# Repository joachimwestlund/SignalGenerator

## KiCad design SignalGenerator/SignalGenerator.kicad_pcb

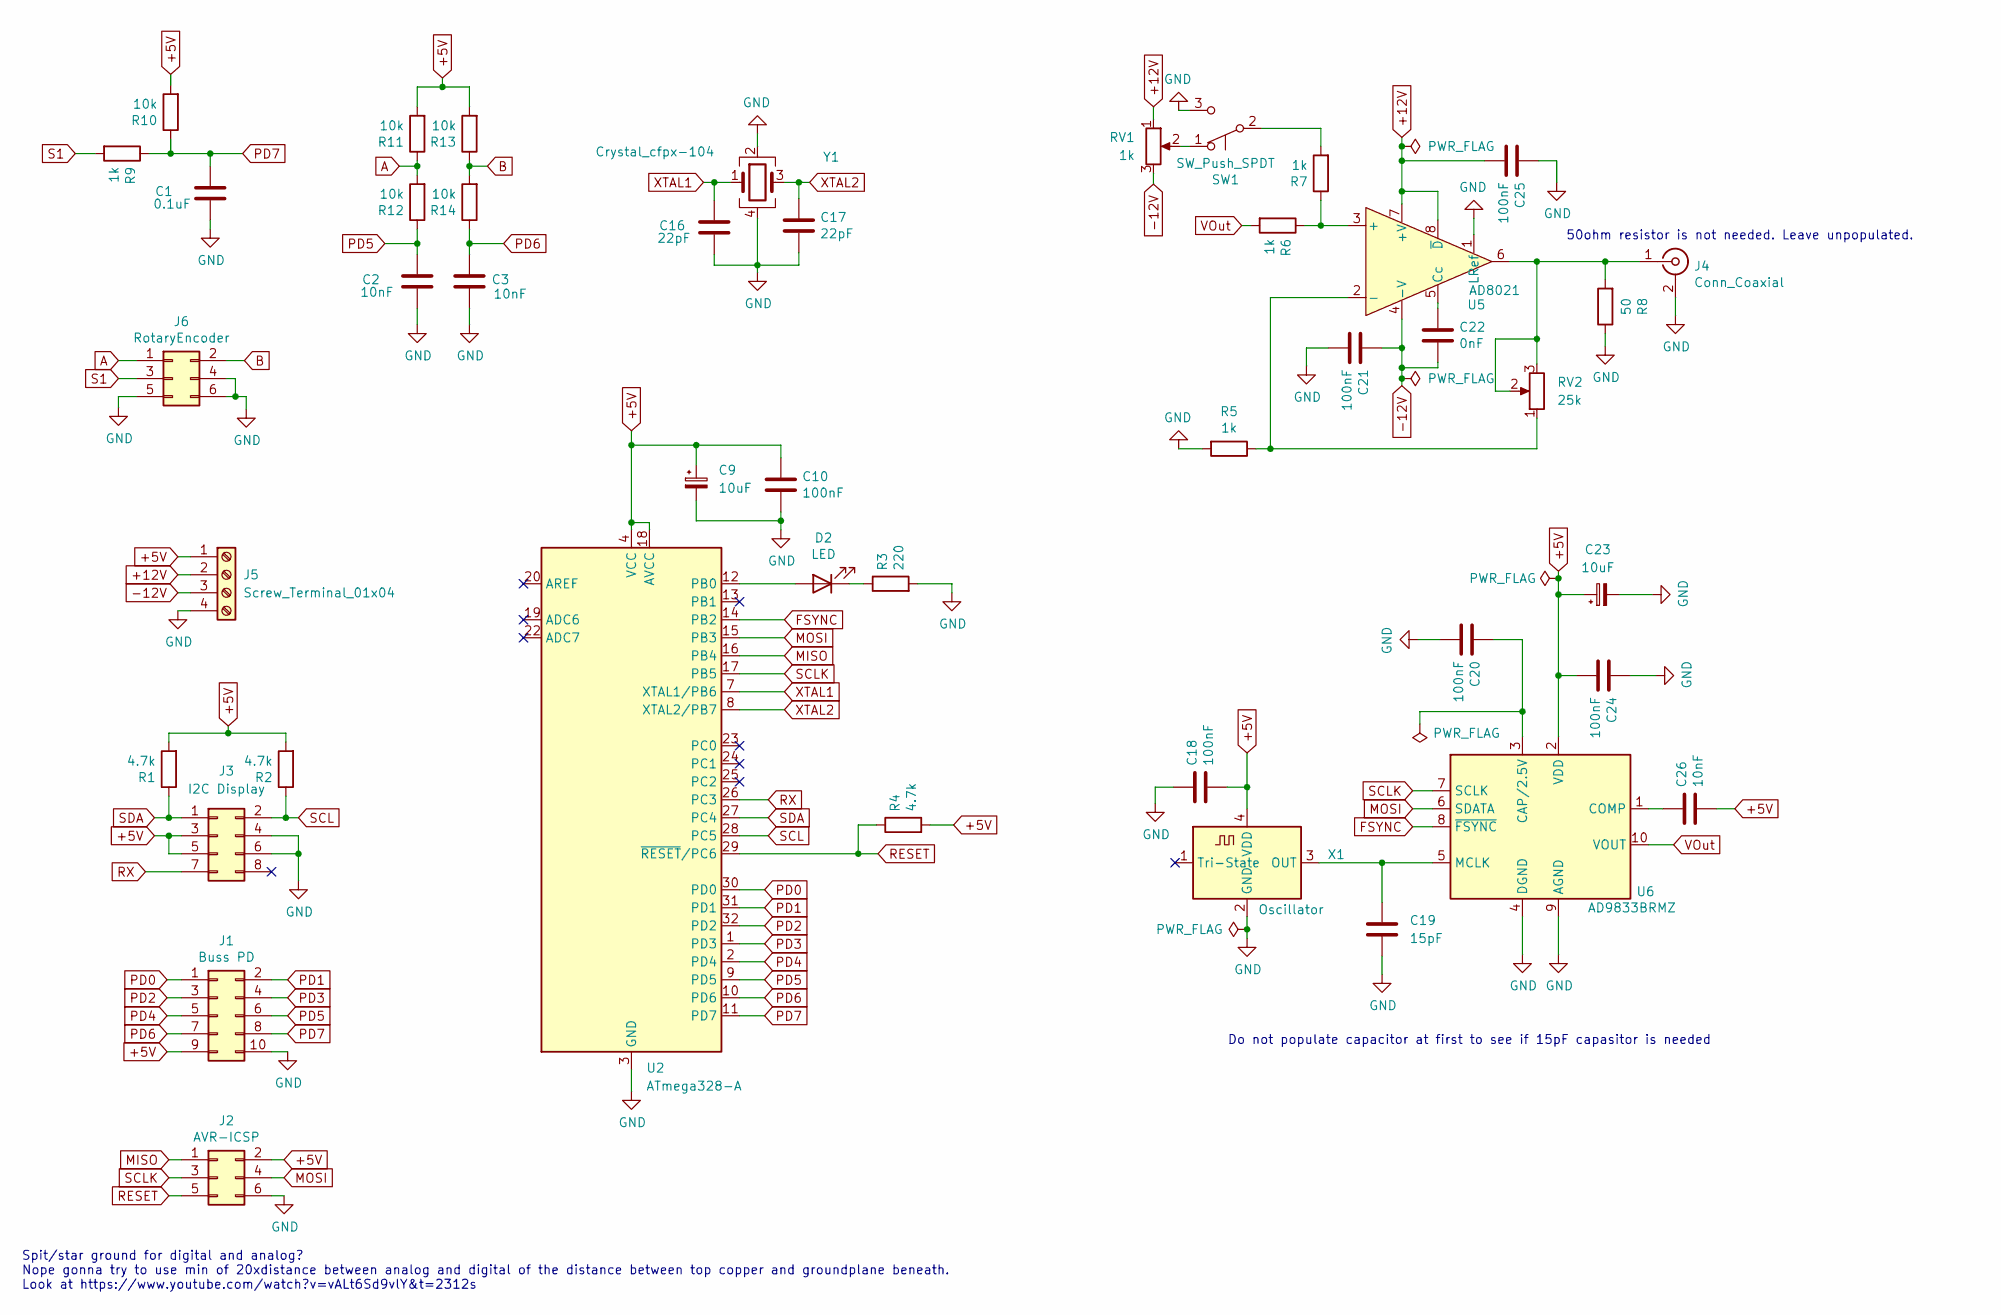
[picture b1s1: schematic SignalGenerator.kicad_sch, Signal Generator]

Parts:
C1: 0.1uF; C_0805_2012Metric_Pad1.18x1.45mm_HandSolder
C2, C3, C26: 10nF; C_1206_3216Metric_Pad1.33x1.80mm_HandSolder
C9, C23: 10uF; CP_EIA-2012-15_AVX-P_Pad1.30x1.05mm_HandSolder; Manuf.# T529P106M010AAE200; LCSC# C696821
C10, C18, C20, C21, C24, C25: 100nF; C_0805_2012Metric_Pad1.18x1.45mm_HandSolder
C16, C17: 22pF; C_0805_2012Metric_Pad1.18x1.45mm_HandSolder
C19: 15pF; C_0805_2012Metric_Pad1.18x1.45mm_HandSolder
C22: 0nF; C_0805_2012Metric_Pad1.18x1.45mm_HandSolder
D2: LED; C_0805_2012Metric_Pad1.18x1.45mm_HandSolder
J1: Buss PD; PinHeader_2x05_P2.54mm_Vertical
J2: AVR-ICSP; PinHeader_2x03_P2.54mm_Vertical
J3: I2C Display; PinHeader_2x04_P2.54mm_Vertical
J4: Conn_Coaxial; PinHeader_1x02_P2.54mm_Vertical; Manuf.# DOSIN-801-0075; LCSC# C521207
J5: Screw_Terminal_01x04; Altech_AK300_1x04_P5.00mm_45-Degree
J6: RotaryEncoder; PinHeader_2x03_P2.54mm_Vertical
R1, R2, R4: 4.7k; R_0805_2012Metric_Pad1.20x1.40mm_HandSolder
R3: 220; R_1206_3216Metric_Pad1.30x1.75mm_HandSolder
R5, R6, R7, R9: 1k; R_0805_2012Metric_Pad1.20x1.40mm_HandSolder
R8: 50; R_0805_2012Metric_Pad1.20x1.40mm_HandSolder
R10, R11, R12, R13, R14: 10k; R_0805_2012Metric_Pad1.20x1.40mm_HandSolder
RV1: 1k; PinHeader_1x03_P2.54mm_Vertical
RV2: 25k; PinHeader_1x03_P2.54mm_Vertical
SW1: SW_Push_SPDT; PinHeader_1x03_P2.54mm_Vertical
U2: ATmega328-A; TQFP-32_7x7mm_P0.8mm
U5: AD8021; SOIC-8_3.9x4.9mm_P1.27mm; Manuf.# AD8021ARZ; LCSC# C17135
U6: AD9833BRMZ; MSOP-10_3x3mm_P0.5mm; Manuf.# AD9833BRMZ; DigiKey# 505-AD9833BRMZ-ND
X1: Oscillator; Oscillator_SMD_Abracon_ASV-4Pin_7.0x5.1mm_HandSoldering; Manuf.# S7D25.000000A20F30T; LCSC# C387028
Y1: Crystal_cfpx-104; Crystal_SMD_5032-4Pin_5.0x3.2mm Handsolder

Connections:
+5V: C9.1, C10.1, C18.2, C23.1, C24.2, C26.2, J1.9, J2.2, J3.3, J3.5, J5.1, R1.2, R2.2, R4.2, R10.2, R11.2, R13.2, U2.4 (VCC), U2.6 (VCC), U2.18 (AVCC), U6.2 (VDD), X1.4 (VDD)
+12V: C25.2, J5.2, RV1.1, U5.7 (+V), U5.8 (~D)
-12V: C21.1, C22.2, J5.3, RV1.3, U5.4 (-V)
A: J6.1, R11.1, R12.2
B: J6.2, R13.1, R14.2
FSYNC: U2.14 (PB2), U6.8 (~FSYNC)
GND: C1.2, C2.2, C3.2, C9.2, C10.2, C16.2, C17.2, C18.1, C19.2, C20.2, C21.2, C23.2, C24.1, C25.1, J1.10, J2.6, J3.4, J3.6, J4.2 (Ext), J5.4, J6.4, J6.5, J6.6, R3.2, R5.2, R8.1, SW1.3 (C), U2.3 (GND), U2.5 (GND), U2.21 (GND), U5.1 (LRef~), U6.4 (DGND), U6.9 (AGND), X1.2 (GND), Y1.2, Y1.4
MISO: J2.1, U2.16 (PB4)
MOSI: J2.4, U2.15 (PB3), U6.6 (SDATA)
unnamed: C19.1, U6.5 (MCLK), X1.3 (OUT)
unnamed: C20.1, U6.3 (CAP/2.5V)
unnamed: C22.1, U5.5 (Cc)
unnamed: C26.1, U6.1 (COMP)
unnamed: D2.1 (K), R3.1
unnamed: D2.2 (A), U2.12 (PB0)
unnamed: J4.1 (In), R8.2, RV2.2, RV2.3, U5.6
unnamed: R5.1, RV2.1, U5.2 (-)
unnamed: R6.1, R7.1, U5.3 (+)
unnamed: R7.2, SW1.2 (B)
unnamed: RV1.2, SW1.1 (A)
PD0: J1.1, U2.30 (PD0)
PD1: J1.2, U2.31 (PD1)
PD2: J1.3, U2.32 (PD2)
PD3: J1.4, U2.1 (PD3)
PD4: J1.5, U2.2 (PD4)
PD5: C2.1, J1.6, R12.1, U2.9 (PD5)
PD6: C3.1, J1.7, R14.1, U2.10 (PD6)
PD7: C1.1, J1.8, R9.1, R10.1, U2.11 (PD7)
RESET: J2.5, R4.1, U2.29 (~RESET/PC6)
RX: J3.7, U2.26 (PC3)
S1: J6.3, R9.2
SCL: J3.2, R2.1, U2.28 (PC5)
SCLK: J2.3, U2.17 (PB5), U6.7 (SCLK)
SDA: J3.1, R1.1, U2.27 (PC4)
VOut: R6.2, U6.10 (VOUT)
XTAL1: C16.1, U2.7 (XTAL1/PB6), Y1.1
XTAL2: C17.1, U2.8 (XTAL2/PB7), Y1.3

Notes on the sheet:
Spit/star ground for digital and analog? Nope gonna try to use min of 20xdistance between analog and digital of the distance between top copper and groundplane beneath. Look at https://www.youtube.com/watch?v=vALt6Sd9vlY&t=2312s
50ohm resistor is not needed. Leave unpopulated.
Do not populate capacitor at first to see if 15pF capasitor is needed

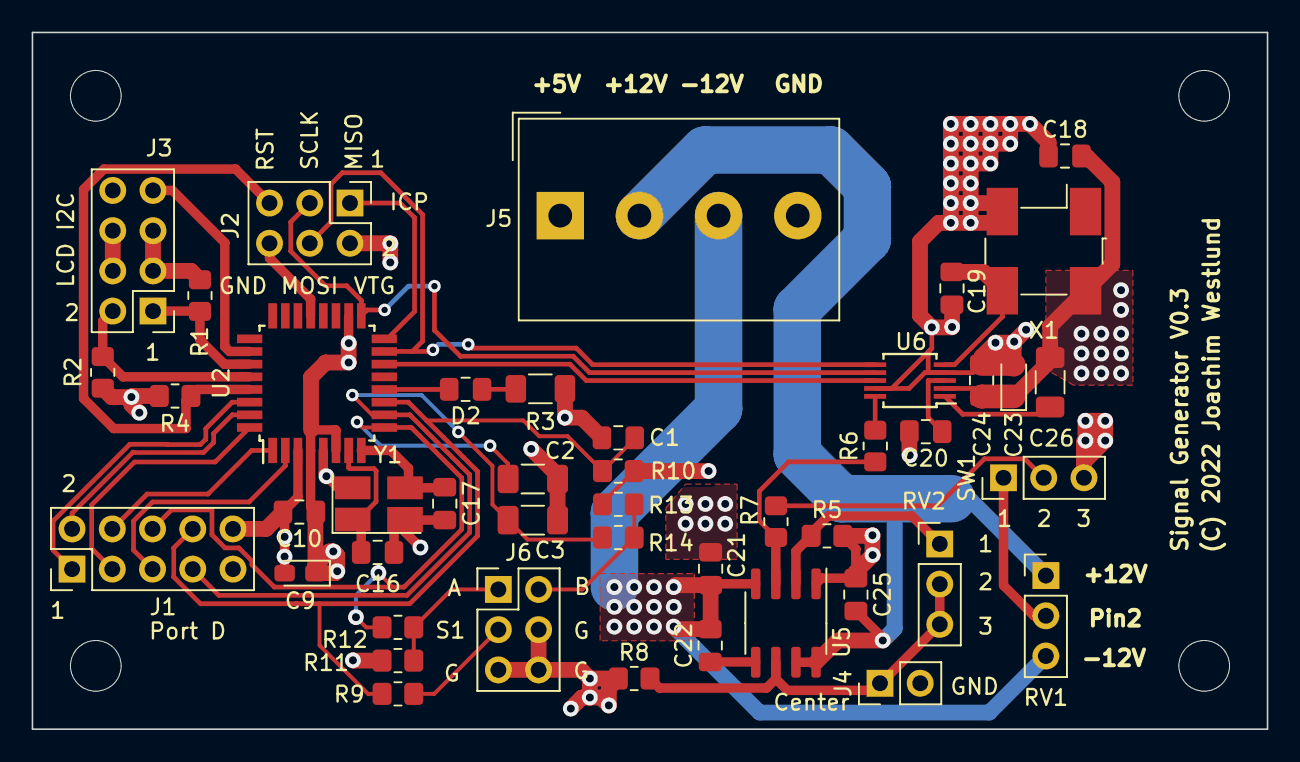
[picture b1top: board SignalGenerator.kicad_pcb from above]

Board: 4 copper layers, 78.0 x 44.0 mm, 45 parts (0 on the bottom side), 37 nets.

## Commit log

2021-11-09 Adding all the files
2021-11-09 Added DC offset to schematic
2021-11-13 doing some small stuff
2021-12-05 Made alot off changes. schematics is much closer to done
2022-02-21 fixing alot of things
2022-02-21 made some stuff again
2022-02-21 test
2022-02-21 Added git igrnore file
2022-02-25 First real revision to the PCB done.
2022-03-08 Adding some software things
2022-03-08 remove a thing
2022-03-08 blinking with stk500
2022-03-11 Added comments
2022-03-11 started to code interrupts for rotary encoder
2022-03-13 Got the I2C working a bit.
2022-03-13 I2C now writes chars and strings to my LCD
2022-03-15 Separeated powersupply to it's own project. Did some stuff to the reset circuit.
2022-03-15 removing stuff
2022-03-15 ignore stuff
2022-03-15 LF to CRLF fix i think
2022-03-15 new logo
2022-03-15 some settings where changed
2022-03-15 gerbers regenerated
2022-03-15 added rotary encoder stuff
2022-03-16 Did alot of changes to my vias. jlcpcb does not support blind or buried vias
2022-03-17 merging drill-files to one for jlcpcb
2022-03-17 regenerating
2022-03-24 trying to code for the signal generator and some gerber updates
2022-03-25 Adding some LCD stuff to the code
2022-03-25 Stuff on rotary encoder and LCD
2022-03-26 Rotary encoder works
2022-03-26 Added rotary encoder button
2022-04-02 added a datasheet and some code
2022-04-02 testing led in software
2022-04-20 adding stuff
2022-04-21 adding code for AD9833. Not working yet
2022-07-05 stuff
2022-07-08 Debuging SPI
2022-07-21 Added schematic pdf and some SPI debuging
2022-10-02 debug project to se what was wrong with SPI code. Now the avr talks and sets up ad9833 correctly

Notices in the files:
SignalGenerator/SignalGenerator.kicad_pcb:
(C) 2022 Joachim Westlund
